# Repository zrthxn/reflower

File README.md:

# Reflow
This is a reflow oven controller based on ideas from ReflowMaster and is intended to work with a kitchen style toaster oven, but can also be adapted to a quartz heater or halogen lamp hack.

### Control Scheme
The MCU first needs to know how fast the temperature rises at full power, as a measure of thermal mass. This value is stored in an internal non-volatile memory.

The based on this, the MCU turns on the load for a certain number of AC cycles, calculated by scaling the duration of the calibration to 10 cycles. After this if the temperature is more than what the calibration curve was, we start reducing the number of cycles. If it is less, we just turn power on and check again after 10 cycles.

This is not a particularly refined or accurate scheme yet, mainly due to my decision to forego having mains voltages on this board and control using SCR phase control.

## Changes from ReflowMaster
I've based this on a more readily available UC3B AVR32 chip rather than an ARM M0 based SAM D21 chip which I think is slightly overkill for something simple like this. 
This could easily be done even with an 8-bit AVR MCU but I chose a 32-bit one simply because of the inbuild USB, preinstalled DFU bootloader, multiple external interrupts, and ease of programming a UI.

## Important Application Notes
http://ww1.microchip.com/downloads/en/devicedoc/doc7745.pdf

## MarcoReps's JBC Station
Marco made a soldering station and used a zero-crossing switching scheme for temperature control. It is very much worth looking at this and improving.
https://www.youtube.com/watch?v=cYgjcDbSyRE

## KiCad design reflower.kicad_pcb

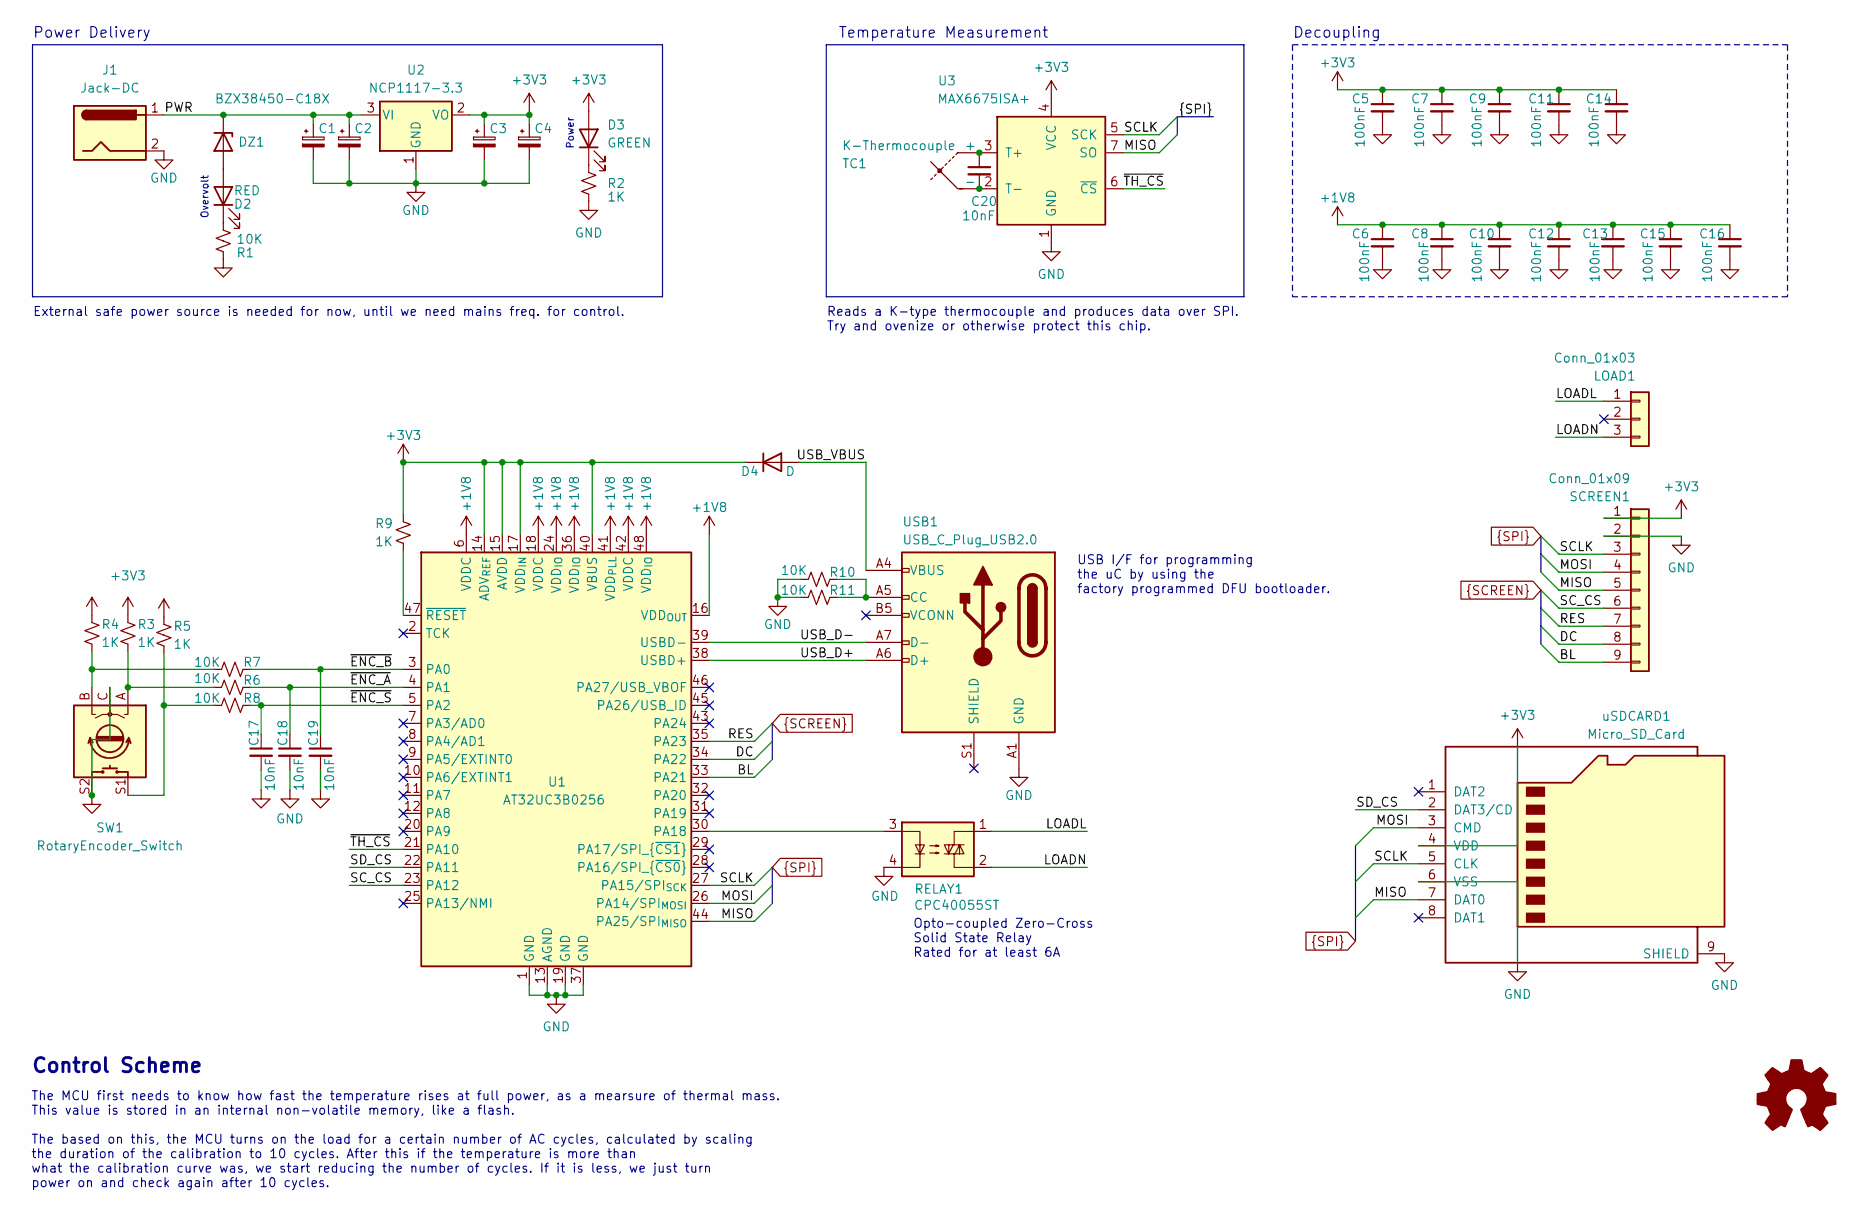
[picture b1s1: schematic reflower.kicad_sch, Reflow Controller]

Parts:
C1, C2, C3, C4: (no value)
C5, C6, C7, C8, C9, C10, C11, C12, C13, C14, C15, C16: 100nF; C_0603_1608Metric
C17, C18, C19, C20: 10nF; C_0603_1608Metric
D2: RED; LED_D3.0mm
D3: GREEN; LED_D3.0mm_Clear
D4: D; D_0603_1608Metric
DZ1: BZX38450-C18X; D_SOD-323
J1: Jack-DC; TerminalBlock_Phoenix_MKDS-1,5-2_1x02_P5.00mm_Horizontal
LOAD1: Conn_01x03; TerminalBlock_Phoenix_MKDS-1,5-3_1x03_P5.00mm_Horizontal
R1, R6, R7, R8, R10, R11: 10K; R_0603_1608Metric
R2, R3, R4, R5, R9: 1K; R_0603_1608Metric
RELAY1: CPC40055ST; IXYS CPC40055ST
SCREEN1: Conn_01x09; PinHeader_1x09_P2.54mm_Horizontal
SW1: RotaryEncoder_Switch; RotaryEncoder_Alps_EC11E-Switch_Vertical_H20mm
TC1: K-Thermocouple; TerminalBlock_Phoenix_MKDS-1,5-2_1x02_P5.00mm_Horizontal
U1: AT32UC3B0256; TQFP-48_7x7mm_P0.5mm
U2: NCP1117-3.3; SOT-223-3_TabPin2
U3: MAX6675ISA+; SOIC-8_3.9x4.9mm_P1.27mm
USB1: USB_C_Plug_USB2.0; USB_C_Receptacle_Amphenol_12401548E4-2A
uSDCARD1: Micro_SD_Card; microSD_HC_Molex_104031-0811

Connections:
+1V8: C6.1, C8.1, C10.1, C12.1, C13.1, C15.1, C16.1, U1.6 (VDDC), U1.16 (VDD_{OUT}), U1.18 (VDDC), U1.24 (VDD_{IO}), U1.36 (VDD_{IO}), U1.41 (VDD_{PLL}), U1.42 (VDDC), U1.48 (VDD_{IO})
+3V3: C3.1, C4.1, C5.1, C7.1, C9.1, C11.1, C14.1, D3.2 (A), D4.1 (K), R3.1, R4.1, R5.1, R9.1, SCREEN1.1, U1.14 (ADV_{REF}), U1.15 (AVDD), U1.17 (VDD_{IN}), U1.40 (VBUS), U2.2 (VO), U3.4 (VCC), uSDCARD1.4 (VDD)
/LOADL: LOAD1.1, RELAY1.1
/LOADN: LOAD1.3, RELAY1.2
/PWR: C1.1, C2.1, DZ1.1 (K), J1.1, U2.3 (VI)
/SD_CS: U1.22 (PA11), uSDCARD1.2 (DAT3/CD)
/USB_D+: U1.38 (USBD+), USB1.A6 (D+)
/USB_D-: U1.39 (USBD-), USB1.A7 (D-)
/USB_VBUS: D4.2 (A), USB1.A4 (VBUS), USB1.A9 (VBUS), USB1.B4 (VBUS), USB1.B9 (VBUS)
/~ENC_A: C18.1, R6.2, U1.4 (PA1)
/~ENC_B: C19.1, R7.2, U1.3 (PA0)
/~ENC_S: C17.1, R8.2, U1.5 (PA2)
/~TH_CS: U1.21 (PA10), U3.6 (~CS)
BL: SCREEN1.9, U1.33 (PA21)
DC: SCREEN1.8, U1.34 (PA22)
GND: C1.2, C2.2, C3.2, C4.2, C5.2, C6.2, C7.2, C8.2, C9.2, C10.2, C11.2, C12.2, C13.2, C14.2, C15.2, C16.2, C17.2, C18.2, C19.2, J1.2, R1.2, R2.2, R10.1, R11.1, RELAY1.4, SCREEN1.2, SW1.C, SW1.S2, U1.1 (GND), U1.13 (AGND), U1.19 (GND), U1.37 (GND), U2.1 (GND), U3.1 (GND), USB1.A1 (GND), USB1.A12 (GND), USB1.B1 (GND), USB1.B12 (GND), uSDCARD1.6 (VSS), uSDCARD1.9 (SHIELD)
MISO: SCREEN1.5, U1.44 (PA25/SPI_{MISO}), U3.7 (SO), uSDCARD1.7 (DAT0)
MOSI: SCREEN1.4, U1.26 (PA14/SPI_{MOSI}), uSDCARD1.3 (CMD)
unnamed: C20.1, TC1.1 (+), U3.3 (T+)
unnamed: C20.2, TC1.2 (-), U3.2 (T-)
unnamed: D2.1 (K), R1.1
unnamed: D2.2 (A), DZ1.2 (A)
unnamed: D3.1 (K), R2.1
unnamed: R3.2, R6.1, SW1.A
unnamed: R4.2, R7.1, SW1.B
unnamed: R5.2, R8.1, SW1.S1
unnamed: R9.2, U1.47 (~RESET)
unnamed: R10.2, R11.2, USB1.A5 (CC)
unnamed: RELAY1.3, U1.30 (PA18)
RES: SCREEN1.7, U1.35 (PA23)
SCLK: SCREEN1.3, U1.27 (PA15/SPI_{SCK}), U3.5 (SCK), uSDCARD1.5 (CLK)
SC_CS: SCREEN1.6, U1.23 (PA12)

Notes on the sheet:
USB I/F for programming the uC by using the factory programmed DFU bootloader.
Control Scheme
Reads a K-type thermocouple and produces data over SPI. Try and ovenize or otherwise protect this chip.
The MCU first needs to know how fast the temperature rises at full power, as a mearsure of thermal mass. This value is stored in an internal non-volatile memory, like a flash. The based on this, the MCU turns on the load for a certain number of AC cycles, calculated by scaling the duration of the c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
Power Delivery
Decoupling
Power
Overvolt
External safe power source is needed for now, until we need mains freq. for control.
Opto-coupled Zero-Cross Solid State Relay Rated for at least 6A
Temperature Measurement

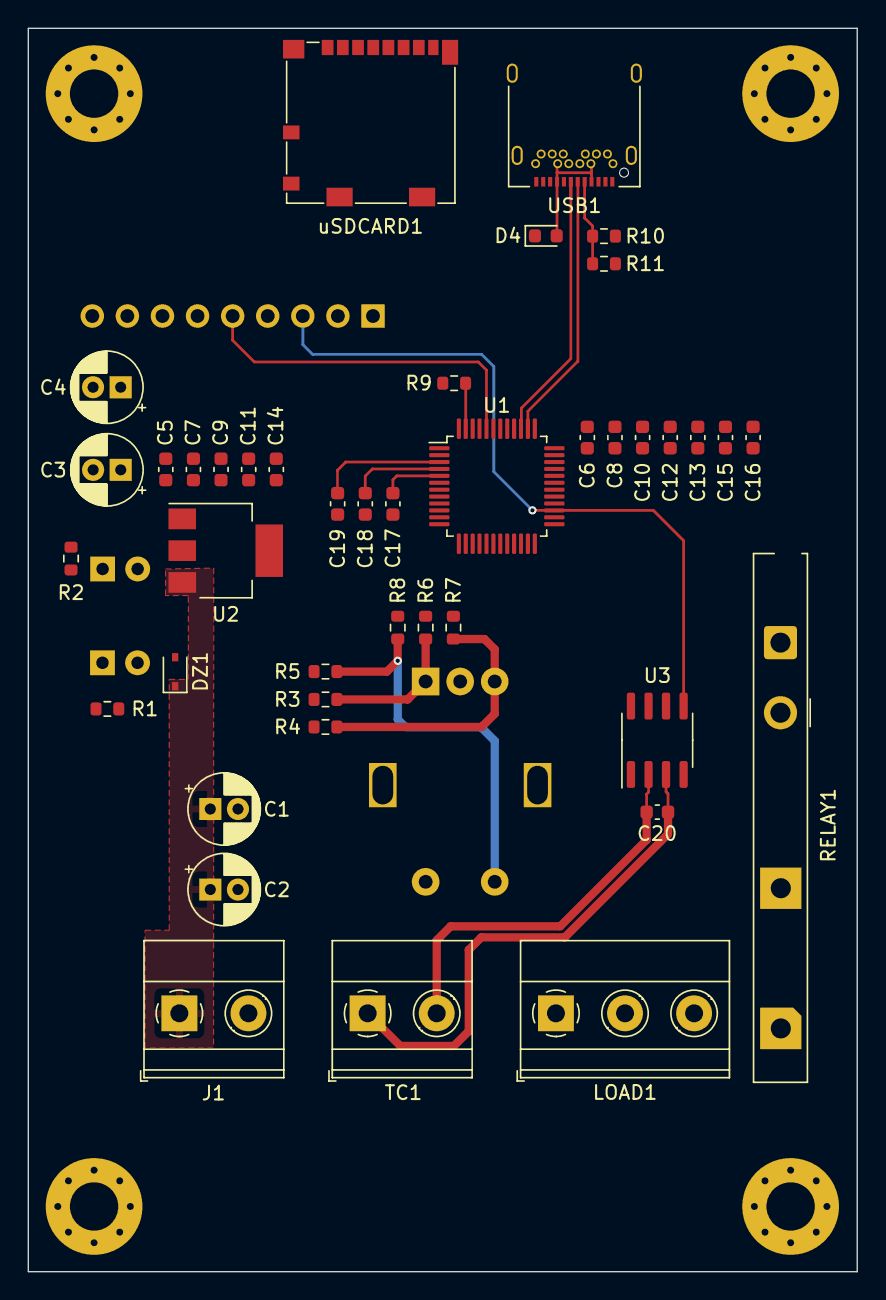
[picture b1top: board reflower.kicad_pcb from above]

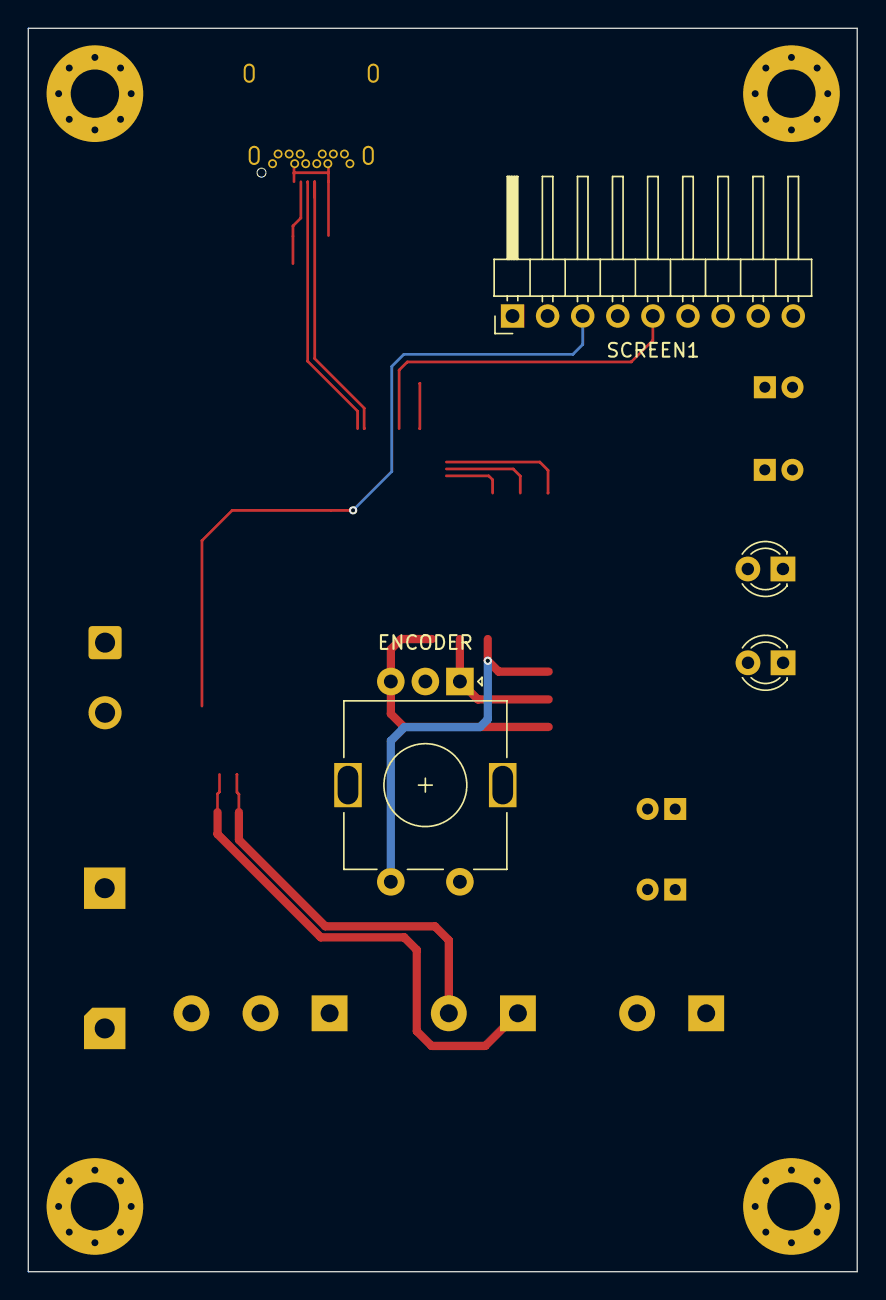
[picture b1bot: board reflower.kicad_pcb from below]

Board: 2 copper layers, 60.0 x 90.0 mm, 46 parts (4 on the bottom side), 32 nets.

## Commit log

2022-05-06 initial plans
2022-05-07 readme
2022-05-08 added separate SD card slot
2022-05-08 schematic improvements
2022-05-08 import RM code
2022-05-28 routing start
2023-08-20 Revise to use STM32
2023-08-21 Redo Power supply
2023-08-21 Power
2023-08-21 External power
2023-09-04 Revisions
